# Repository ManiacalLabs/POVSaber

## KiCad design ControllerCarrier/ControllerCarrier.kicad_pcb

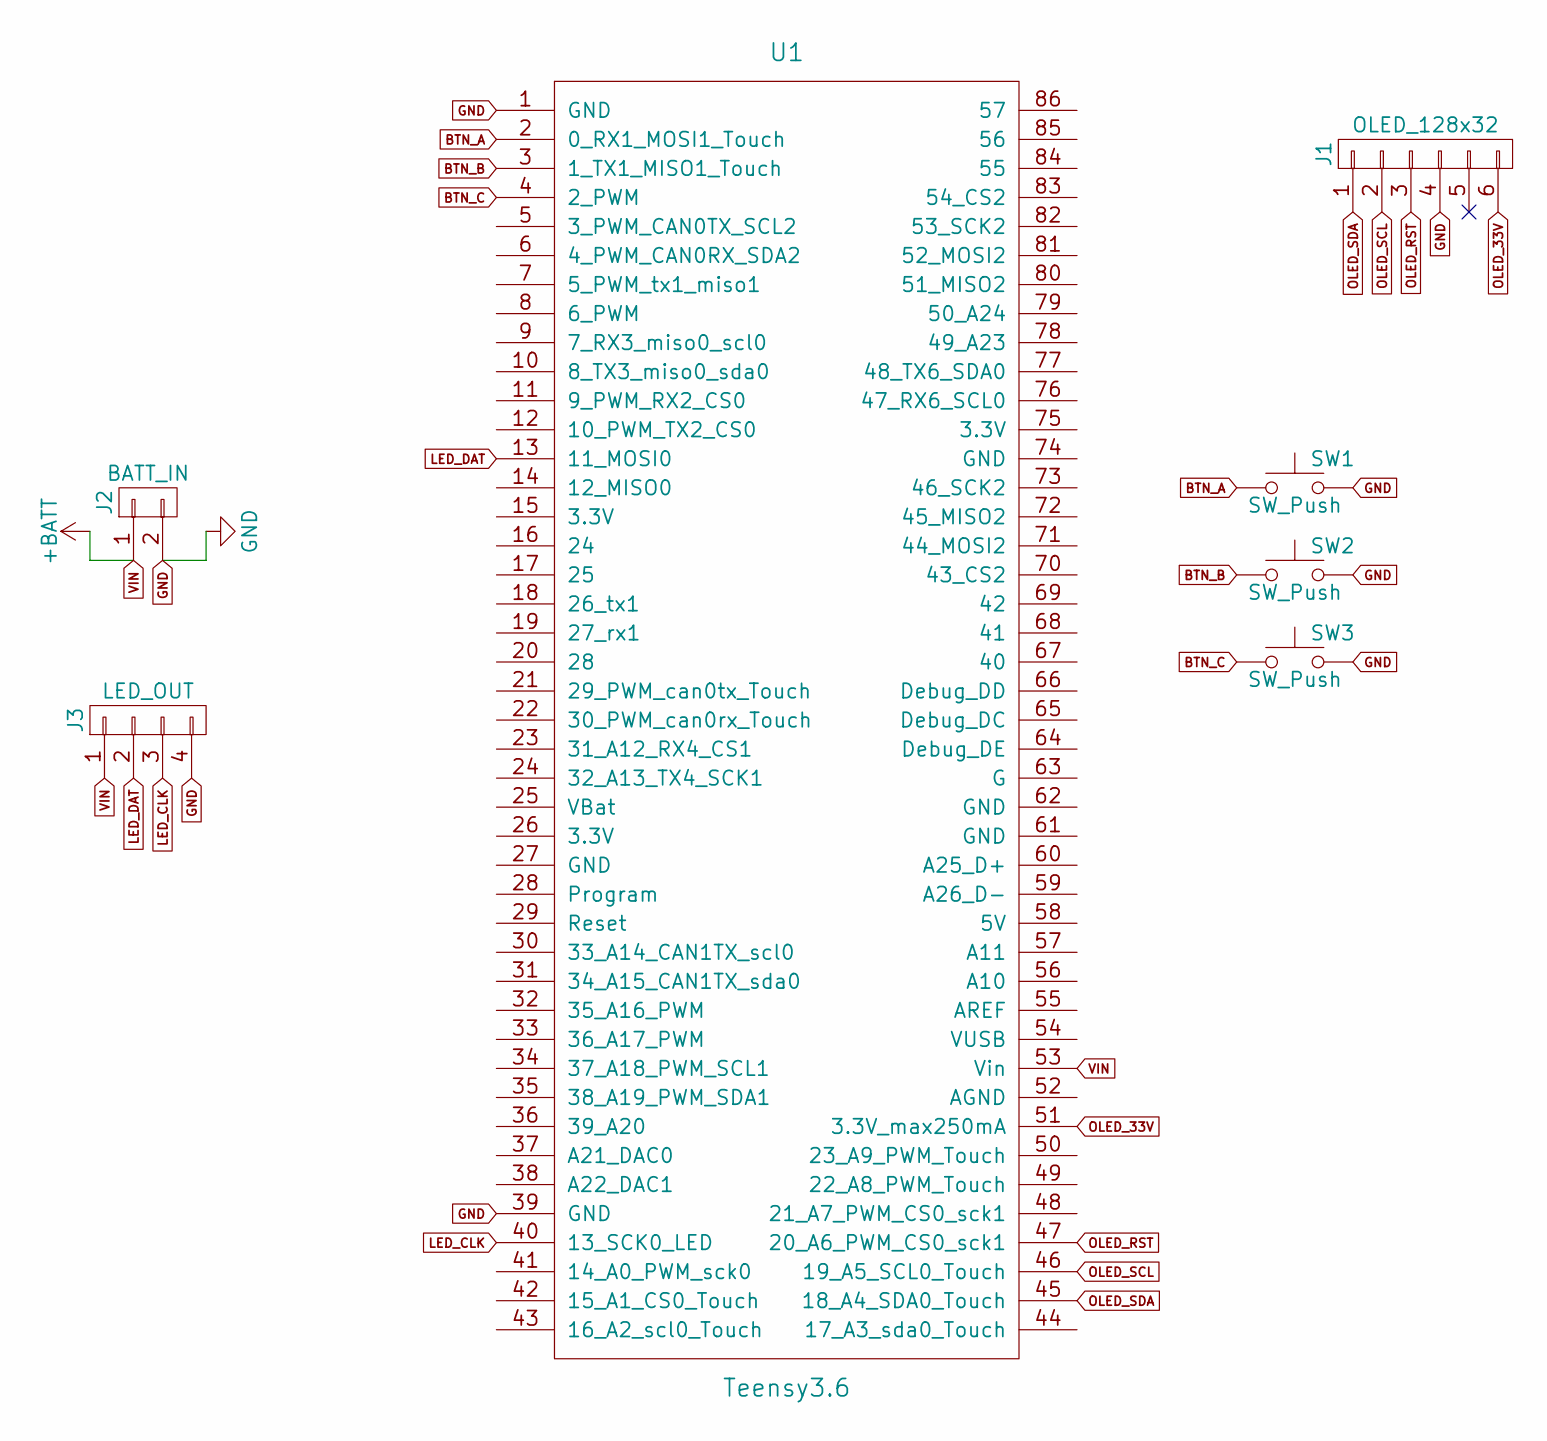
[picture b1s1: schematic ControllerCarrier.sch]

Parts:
J1: OLED_128x32; OLED_128x32_i2c
J2: BATT_IN; Pin_Header_Straight_1x02_Pitch2.54mm
J3: LED_OUT; Pin_Header_Straight_1x04_Pitch2.54mm
SW1, SW2, SW3: SW_Push; PCB_PUSH
U1: Teensy3.6; Teensy35_36

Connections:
BTN_A: SW1.1, U1.2 (0_RX1_MOSI1_Touch)
BTN_B: SW2.1, U1.3 (1_TX1_MISO1_Touch)
BTN_C: SW3.1, U1.4 (2_PWM)
GND: J1.4, J2.2, J3.4, SW1.2, SW2.2, SW3.2, U1.1 (GND), U1.39 (GND)
LED_CLK: J3.3, U1.40 (13_SCK0_LED)
LED_DAT: J3.2, U1.13 (11_MOSI0)
OLED_33V: J1.6, U1.51 (3.3V_max250mA)
OLED_RST: J1.3, U1.47 (20_A6_PWM_CS0_sck1)
OLED_SCL: J1.2, U1.46 (19_A5_SCL0_Touch)
OLED_SDA: J1.1, U1.45 (18_A4_SDA0_Touch)
VIN: J2.1, J3.1, U1.53 (Vin)

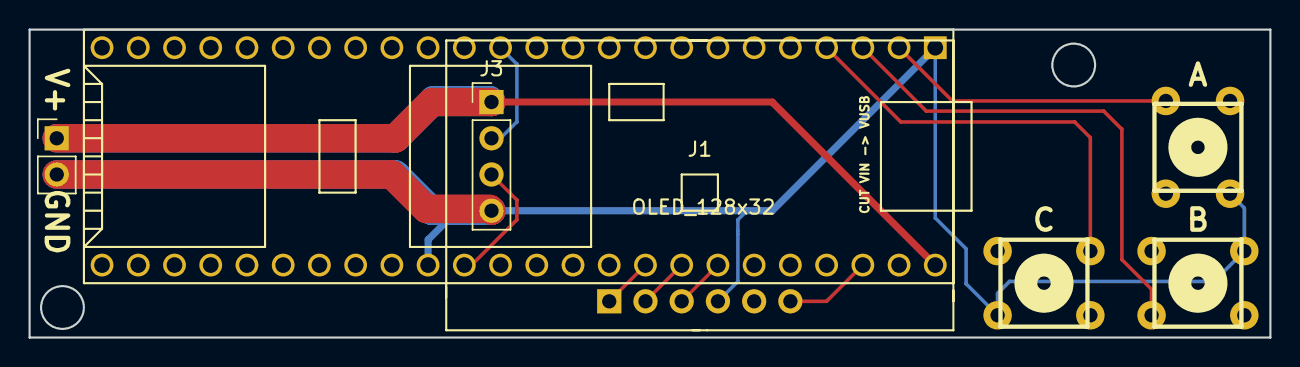
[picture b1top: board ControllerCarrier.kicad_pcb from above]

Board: 2 copper layers, 87.0 x 21.6 mm, 7 parts (0 on the bottom side), 11 nets.

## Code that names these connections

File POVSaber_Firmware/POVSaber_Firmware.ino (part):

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}

// Button Stuff
#define BTN_A 0
#define BTN_B 1
#define BTN_C 2
#define BTN_INTERVAL 5

typedef struct __attribute__((__packed__))
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Bounce btn_c = Bounce();

inline void setup_btns(){
    pinMode(BTN_A, INPUT_PULLUP);
    pinMode(BTN_B, INPUT_PULLUP);
    pinMode(BTN_C, INPUT_PULLUP);

    btn_a.attach(BTN_A);
    btn_a.interval(BTN_INTERVAL);
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
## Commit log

2017-07-01 works reading SD and displaying to strip
2017-07-01 added oled display
2017-07-01 Adding button handler
2017-07-02 Selectable files now
2017-07-02 Get FPS from file extension
2017-07-02 Added brightness menu
2017-07-02 bright menu is now rainbow
2017-07-02 don't change menu item when off menu
2017-07-02 no more delay for frame time
2017-07-02 Added saber modes
2017-07-05 Added controller PCB
2017-07-28 Updated to use constant current scale
2017-08-20 firmware tweaks and new images
2017-08-22 Verification images exported
2017-08-22 Added more anims
